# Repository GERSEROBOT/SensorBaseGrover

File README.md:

# SensorBaseGrover

If it is necessary to download the MyKiCad repository, it is a library and contains components that this project can use
	- https://github.com/pedro-ibs/MyKiCad

-------------------------------------------------------------------------------------------------------------------------------

Here are the sensors used for Shield Sensor Base Grover GERSE:
	- https://github.com/GERSEROBOT/ShieldSensorBaseGroverGERSE

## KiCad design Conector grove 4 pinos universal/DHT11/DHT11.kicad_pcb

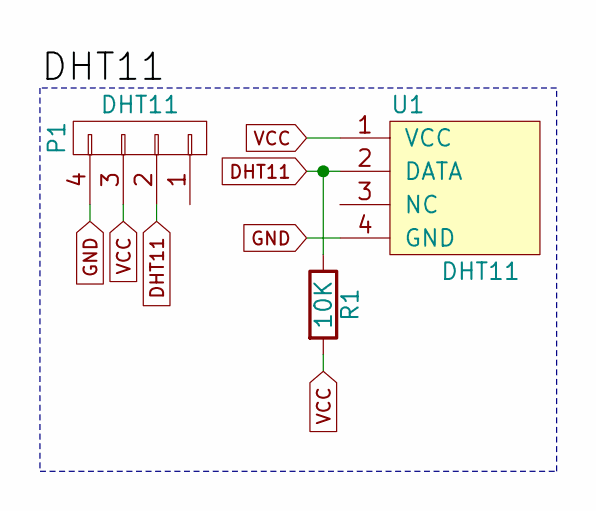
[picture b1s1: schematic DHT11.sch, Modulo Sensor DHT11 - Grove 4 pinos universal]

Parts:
P1: DHT11; Grove 4 pinos
R1: 10K; Resistor_Vertical_RM3mm
U1: DHT11

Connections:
DHT11: P1.2, R1.1, U1.2 (DATA)
GND: P1.4, U1.4 (GND)
VCC: P1.3, R1.2, U1.1 (VCC)

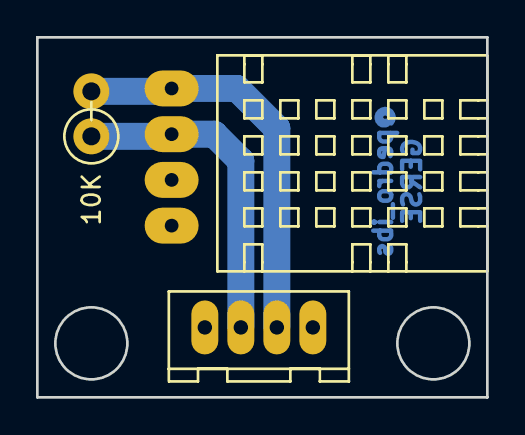
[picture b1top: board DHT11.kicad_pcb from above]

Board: 2 copper layers, 25.0 x 20.0 mm, 3 parts (0 on the bottom side), 3 nets.

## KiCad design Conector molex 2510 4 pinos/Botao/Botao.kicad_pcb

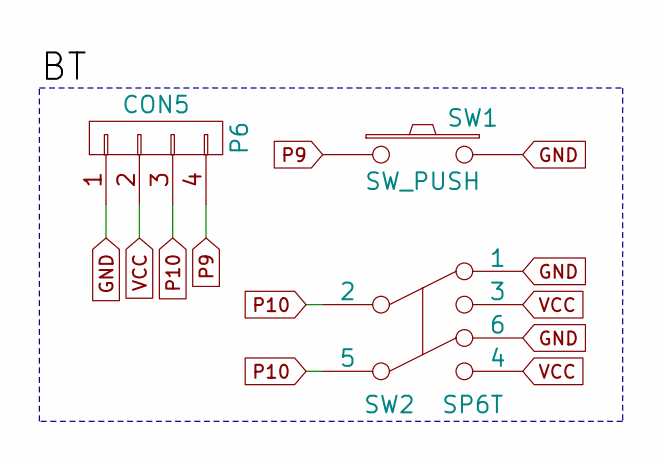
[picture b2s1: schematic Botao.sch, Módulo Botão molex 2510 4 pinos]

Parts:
P6: CON5; molex_2510
SW1: SW_PUSH; BUTTON2P
SW2: SP6T; SW_PUSH_x2

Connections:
GND: P6.1, SW1.2, SW2.1, SW2.6
P9: P6.4, SW1.1
P10: P6.3, SW2.2, SW2.5
VCC: P6.2, SW2.3, SW2.4

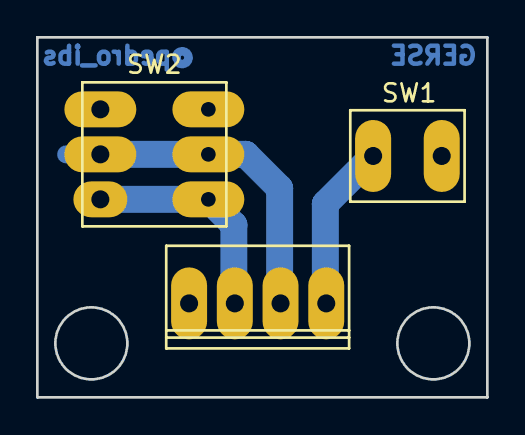
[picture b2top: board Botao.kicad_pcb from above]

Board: 2 copper layers, 25.0 x 20.0 mm, 3 parts (0 on the bottom side), 4 nets.

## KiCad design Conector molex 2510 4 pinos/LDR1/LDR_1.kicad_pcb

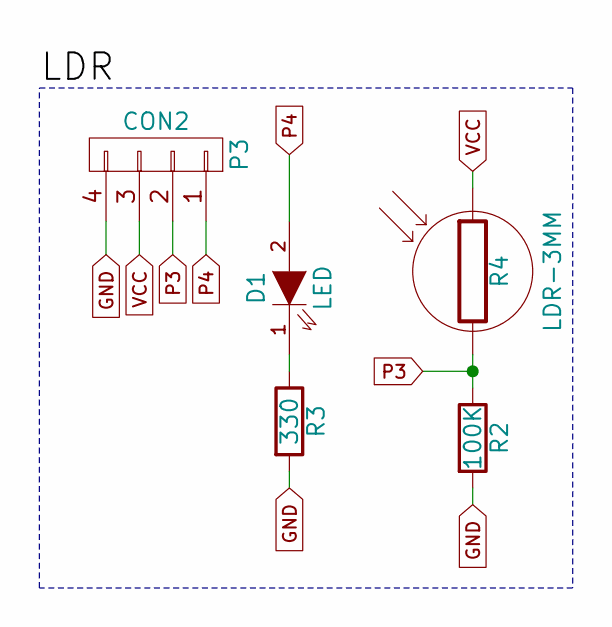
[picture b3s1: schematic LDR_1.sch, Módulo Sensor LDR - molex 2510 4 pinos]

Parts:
D1: LED; LED-3MM
P3: CON2; molex_2510
R2: 100K; Resistor_Horizontal_RM10mm
R3: 330; Resistor_Horizontal_RM10mm
R4: LDR-3MM; LDR3mm

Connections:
GND: P3.4, R2.2, R3.2
unnamed: D1.1 (K), R3.1
P3: P3.2, R2.1, R4.2
P4: D1.2 (A), P3.1
VCC: P3.3, R4.1

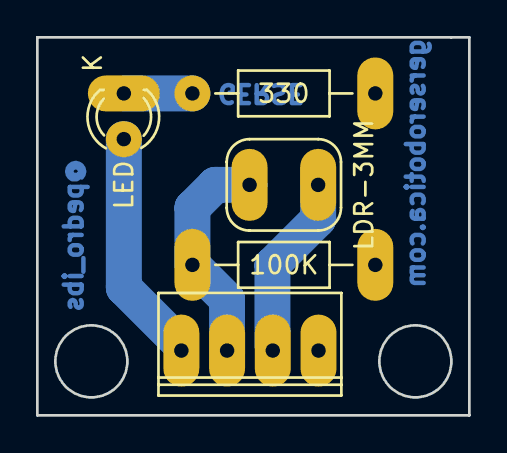
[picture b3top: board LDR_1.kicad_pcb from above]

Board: 2 copper layers, 24.0 x 21.0 mm, 5 parts (0 on the bottom side), 5 nets.

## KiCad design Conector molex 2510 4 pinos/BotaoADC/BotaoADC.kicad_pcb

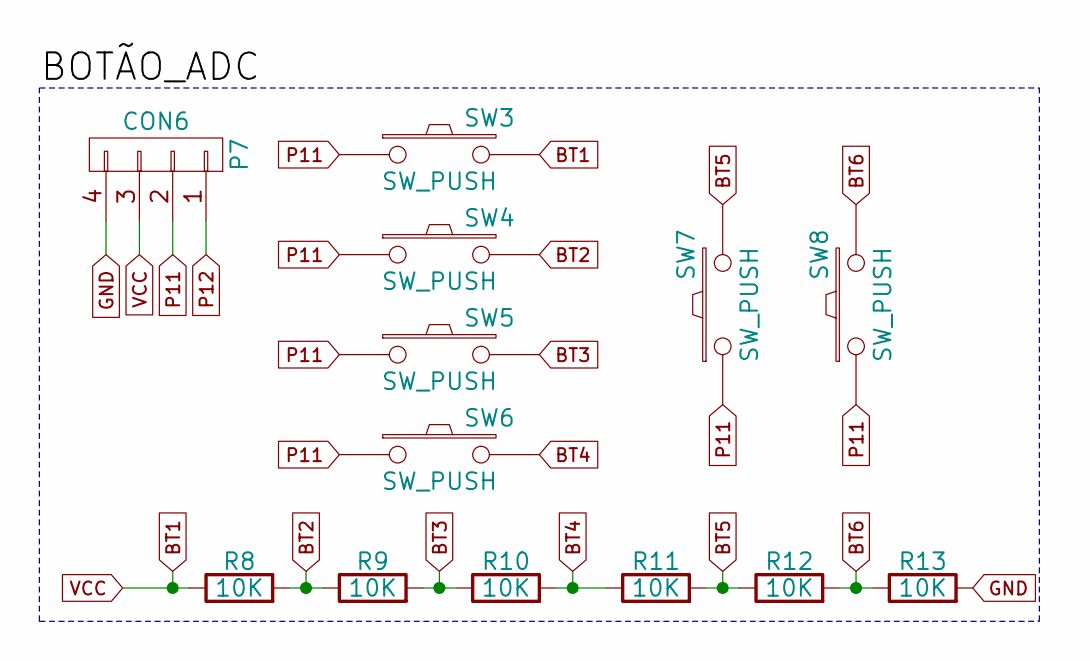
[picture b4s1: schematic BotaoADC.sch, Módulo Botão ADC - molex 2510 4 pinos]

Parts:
P7: CON6; molex_2510
R8, R9, R10, R11, R12, R13: 10K; Resistor_Horizontal_RM10mm
SW3, SW4, SW5, SW6, SW7, SW8: SW_PUSH; BUTTON2P

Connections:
BT1: P7.3, R8.1, SW3.2
BT2: R8.2, R9.1, SW4.2
BT3: R9.2, R10.1, SW5.2
BT4: R10.2, R11.1, SW6.2
BT5: R11.2, R12.1, SW7.2
BT6: R12.2, R13.1, SW8.2
GND: P7.4, R13.2
P11: P7.2, SW3.1, SW4.1, SW5.1, SW6.1, SW7.1, SW8.1
P12: P7.1

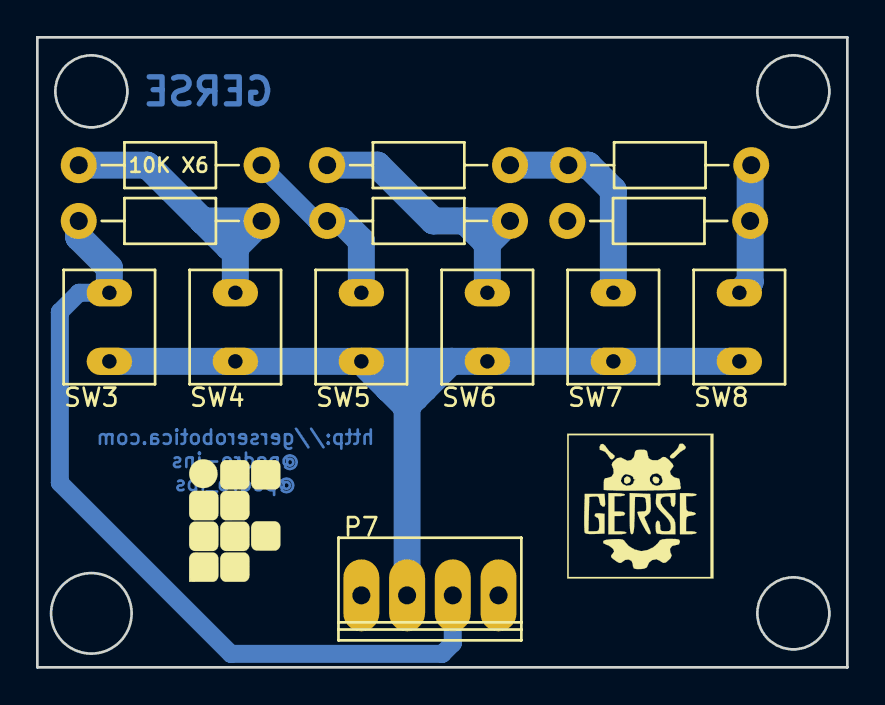
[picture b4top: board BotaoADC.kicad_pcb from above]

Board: 2 copper layers, 45.0 x 35.0 mm, 13 parts (0 on the bottom side), 8 nets.

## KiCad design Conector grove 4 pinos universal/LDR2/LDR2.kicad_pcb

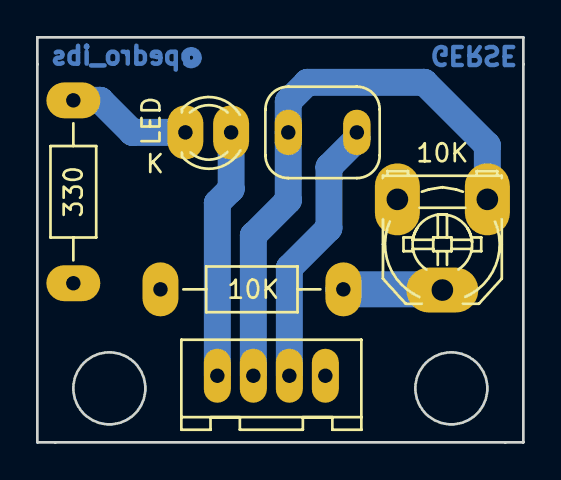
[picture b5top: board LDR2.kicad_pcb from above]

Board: 2 copper layers, 27.0 x 22.5 mm, 6 parts (0 on the bottom side), 6 nets.

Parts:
D2: LED; LED-3MM
P4: CON3; Grove 4 pinos
R5: 330; Resistor_Horizontal_RM10mm
R6: 10K; Resistor_Horizontal_RM10mm
R7: LDR-3MM; LDR3mm
RV1: 10K; Potentiometer_Triwood_RM-065

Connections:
GND: P4.4, R5.2, R6.2
unnamed: D2.1, R5.1
unnamed: R6.1, RV1.2
P5: P4.2, R7.2, RV1.1
P6: D2.2, P4.1
VCC: P4.3, R7.1

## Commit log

2017-08-31 Qui Ago 31 16:31:14 BRT 2017
2017-09-05 Ter Set 5 18:53:25 BRT 2017
2017-09-11 Connector patch
